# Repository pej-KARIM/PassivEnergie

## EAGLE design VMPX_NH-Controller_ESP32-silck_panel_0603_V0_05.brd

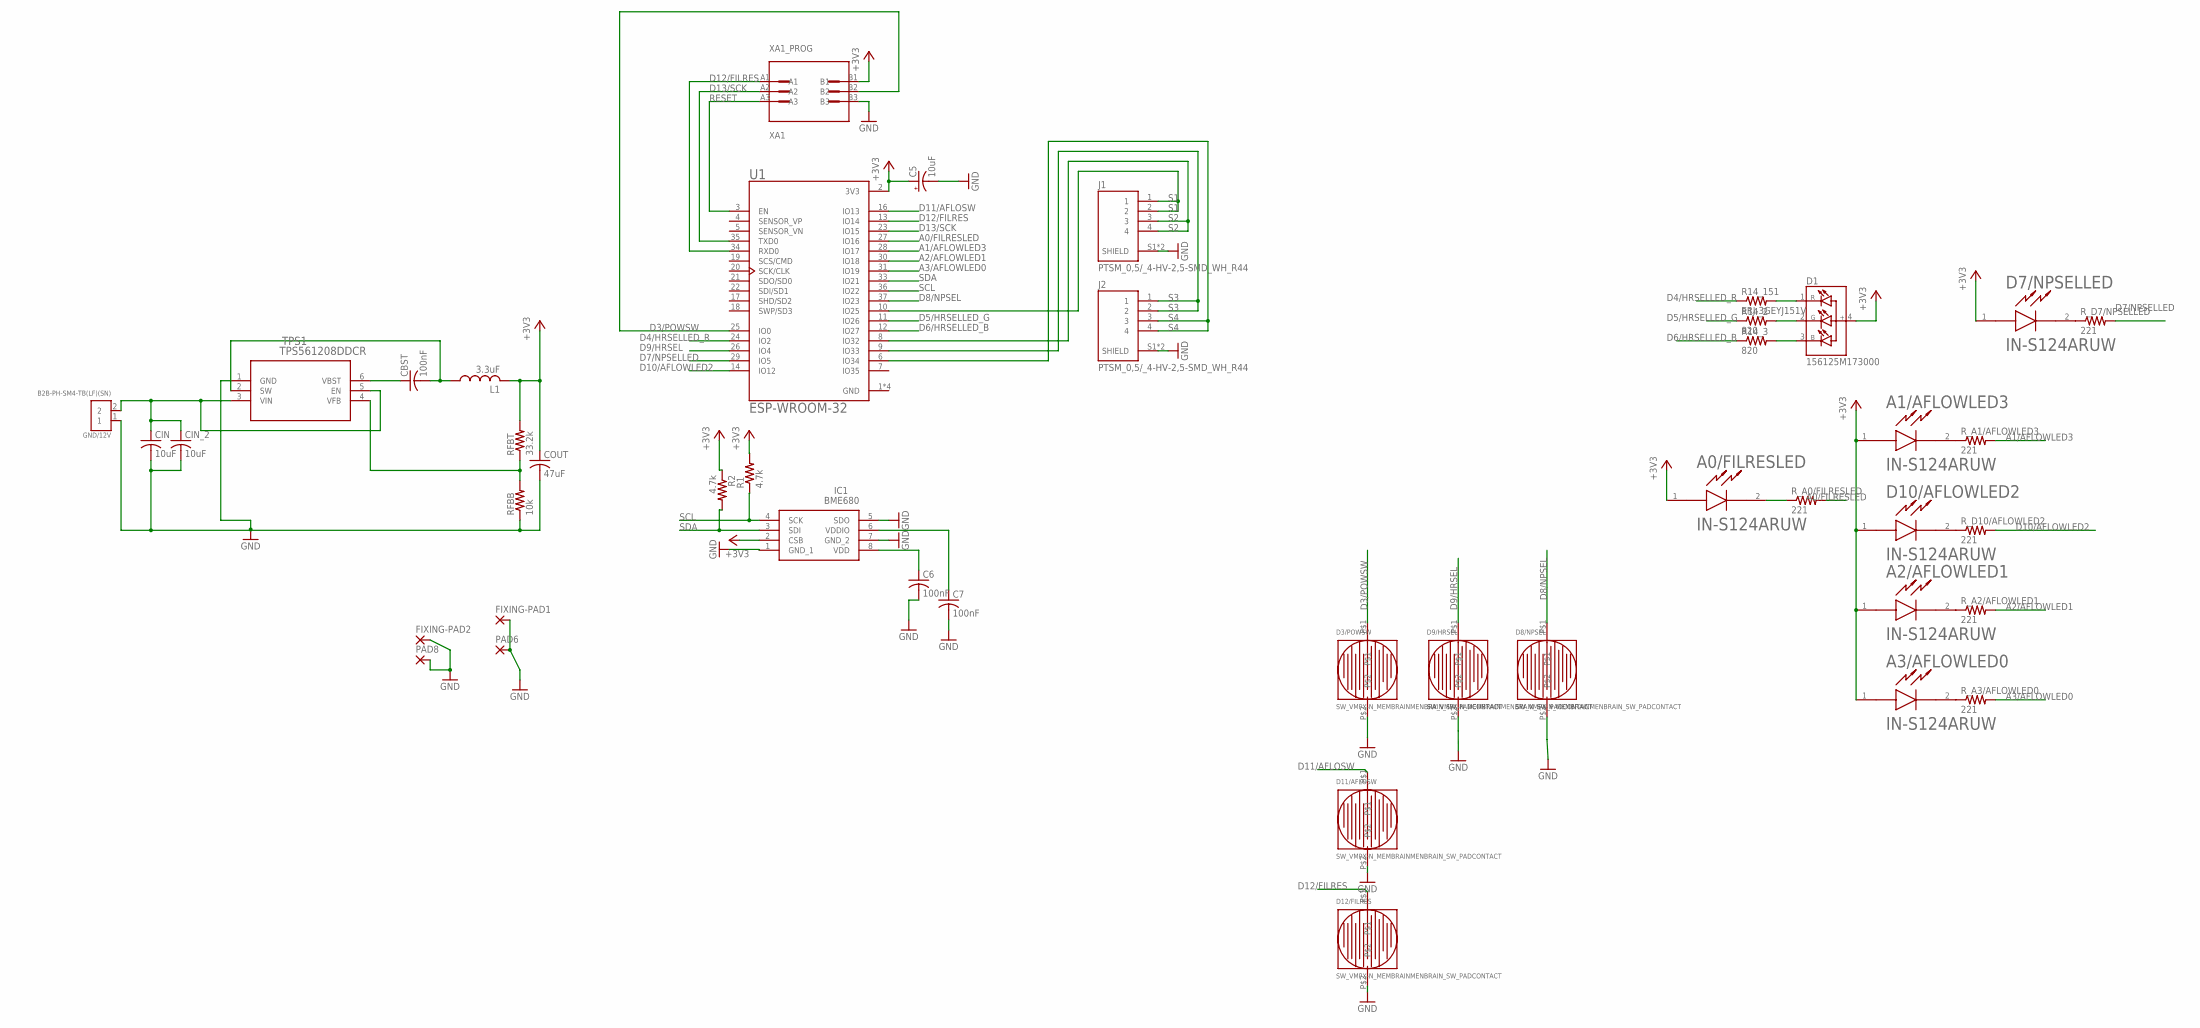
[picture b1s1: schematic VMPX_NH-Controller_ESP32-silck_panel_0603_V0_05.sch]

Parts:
A0/FILRESLED, A1/AFLOWLED3, A2/AFLOWLED1, A3/AFLOWLED0: IN-S124ARUW; LED_IN-S124ARUW
C5: 10uF; EIA3216
C6, C7: 100nF; C0603
CBST: 100nF; C0603
CIN: 10uF; C0603
CIN_2: 10uF; C0603
COUT: 47uF; C0603
D1: 156125M173000; LED_156125M173000
D3/POWSW, D8/NPSEL, D9/HRSEL, D11/AFLOSW, D12/FILRES: SW_VMPX-N_MEMBRAINMENBRAIN_SW_PADCONTACT; MENBRANSWITCHCONTACT
D7/NPSELLED, D10/AFLOWLED2: IN-S124ARUW; LED_IN-S124ARUW
FIXING-PAD1, FIXING-PAD2: SMD5; SMD2,54-5,08
GND/12V: B2B-PH-SM4-TB(LF)(SN); JST_B2B-PH-SM4-TB(LF)(SN)
IC1: BME680
J1, J2: PTSM_0,5/_4-HV-2,5-SMD_WH_R44; PHOENIX_PTSM_0,5/_4-HV-2,5-SMD_WH_R44
L1: 3.3uF; L2012C
PAD6, PAD8: SMD5; SMD2,54-5,08
R1, R2: 4.7k; RESC1608X55
R14_2, R14_3: 820; RESC1608X55
R14_151: ERJ-3GEYJ151V; RESC1608X55
RFBB: 10k; R0603
RFBT: 33.2k; R0603
R_A0/FILRESLED, R_A1/AFLOWLED3, R_A2/AFLOWLED1, R_A3/AFLOWLED0: 221; RESC1608X55
R_D7/NPSELLED, R_D10/AFLOWLED2: 221; RESC1608X55
TPS1: TPS561208DDCR; DDC6
U1: ESP-WROOM-32; MODULE_ESP-WROOM-32
XA1_PROG: XA1; TE_5-146130-2

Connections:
+3V3: A0/FILRESLED.1 (A), A1/AFLOWLED3.1 (A), A2/AFLOWLED1.1 (A), A3/AFLOWLED0.1 (A), C5.A (+), COUT.1, D1.4 (+), D7/NPSELLED.1 (A), D10/AFLOWLED2.1 (A), IC1.2 (CSB), L1.2, R1.2, R2.1, RFBT.2, U1.2 (3V3), XA1_PROG.B1
A0/FILRESLED: R_A0/FILRESLED.2, U1.27 (IO16)
A1/AFLOWLED3: R_A1/AFLOWLED3.2, U1.28 (IO17)
A2/AFLOWLED1: R_A2/AFLOWLED1.2, U1.30 (IO18)
A3/AFLOWLED0: R_A3/AFLOWLED0.2, U1.31 (IO19)
D3/POWSW: D3/POWSW.P$1, U1.25 (IO0), XA1_PROG.B2
D4/HRSELLED_R: R14_151.1, U1.24 (IO2)
D5/HRSELLED_G: R14_2.1, U1.11 (IO26)
D6/HRSELLED_B: R14_3.1, U1.12 (IO27)
D7/NPSELLED: R_D7/NPSELLED.2, U1.29 (IO5)
D8/NPSEL: D8/NPSEL.P$1, U1.37 (IO23)
D9/HRSEL: D9/HRSEL.P$1, U1.26 (IO4)
D10/AFLOWLED2: R_D10/AFLOWLED2.2, U1.14 (IO12)
D11/AFLOSW: D11/AFLOSW.P$1, U1.16 (IO13)
D12/FILRES: D12/FILRES.P$1, U1.13 (IO14), U1.34 (RXD0), XA1_PROG.A1
D13/SCK: U1.23 (IO15), U1.35 (TXD0), XA1_PROG.A2
GND: C5.C (-), C6.2, C7.2, CIN.2, CIN_2.2, COUT.2, D3/POWSW.P$2, D8/NPSEL.P$2, D9/HRSEL.P$2, D11/AFLOSW.P$2, D12/FILRES.P$2, FIXING-PAD1.1, FIXING-PAD2.1, GND/12V.1, IC1.1 (GND_1), IC1.5 (SDO), IC1.7 (GND_2), J1.S1 (SHIELD), J1.S2 (SHIELD), J2.S1 (SHIELD), J2.S2 (SHIELD), PAD6.1, PAD8.1, RFBB.1, TPS1.1 (GND), U1.1 (GND), U1.1.1 (GND), U1.15 (GND), U1.38 (GND), XA1_PROG.B3
unnamed: A0/FILRESLED.2 (C), R_A0/FILRESLED.1
unnamed: C6.1, IC1.8 (VDD)
unnamed: D1.2 (G-), R14_2.2
unnamed: C7.1, IC1.6 (VDDIO)
unnamed: D1.3 (B-), R14_3.2
unnamed: D1.1 (R-), R14_151.2
unnamed: D7/NPSELLED.2 (C), R_D7/NPSELLED.1
unnamed: D10/AFLOWLED2.2 (C), R_D10/AFLOWLED2.1
unnamed: A1/AFLOWLED3.2 (C), R_A1/AFLOWLED3.1
unnamed: A2/AFLOWLED1.2 (C), R_A2/AFLOWLED1.1
unnamed: A3/AFLOWLED0.2 (C), R_A3/AFLOWLED0.1
RESET: U1.3 (EN), XA1_PROG.A3
S1: J1.1, J1.2, U1.10 (IO25)
S2: J1.3, J1.4, U1.8 (IO32)
S3: J2.1, J2.2, U1.9 (IO33)
S4: J2.3, J2.4, U1.6 (IO34)
SCL: IC1.4 (SCK), R1.1, U1.36 (IO22)
SDA: IC1.3 (SDI), R2.2, U1.33 (IO21)
SW: CBST.2, L1.1, TPS1.2 (SW)
VBF: RFBB.2, RFBT.1, TPS1.4 (VFB)
VBST: CBST.1, TPS1.6 (VBST)
VIN: CIN.1, CIN_2.1, GND/12V.2, TPS1.3 (VIN), TPS1.5 (EN)

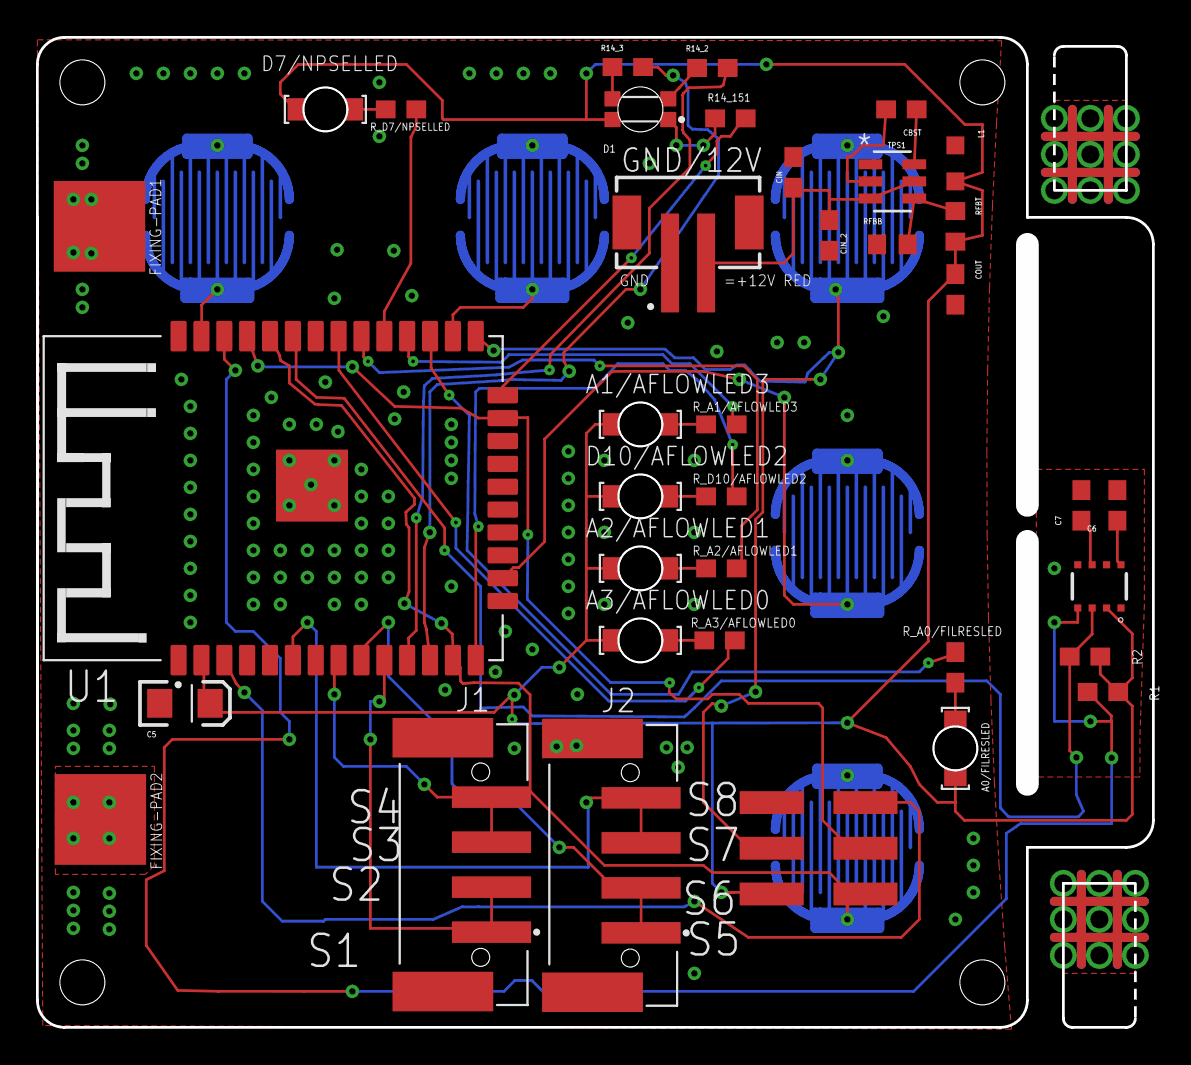
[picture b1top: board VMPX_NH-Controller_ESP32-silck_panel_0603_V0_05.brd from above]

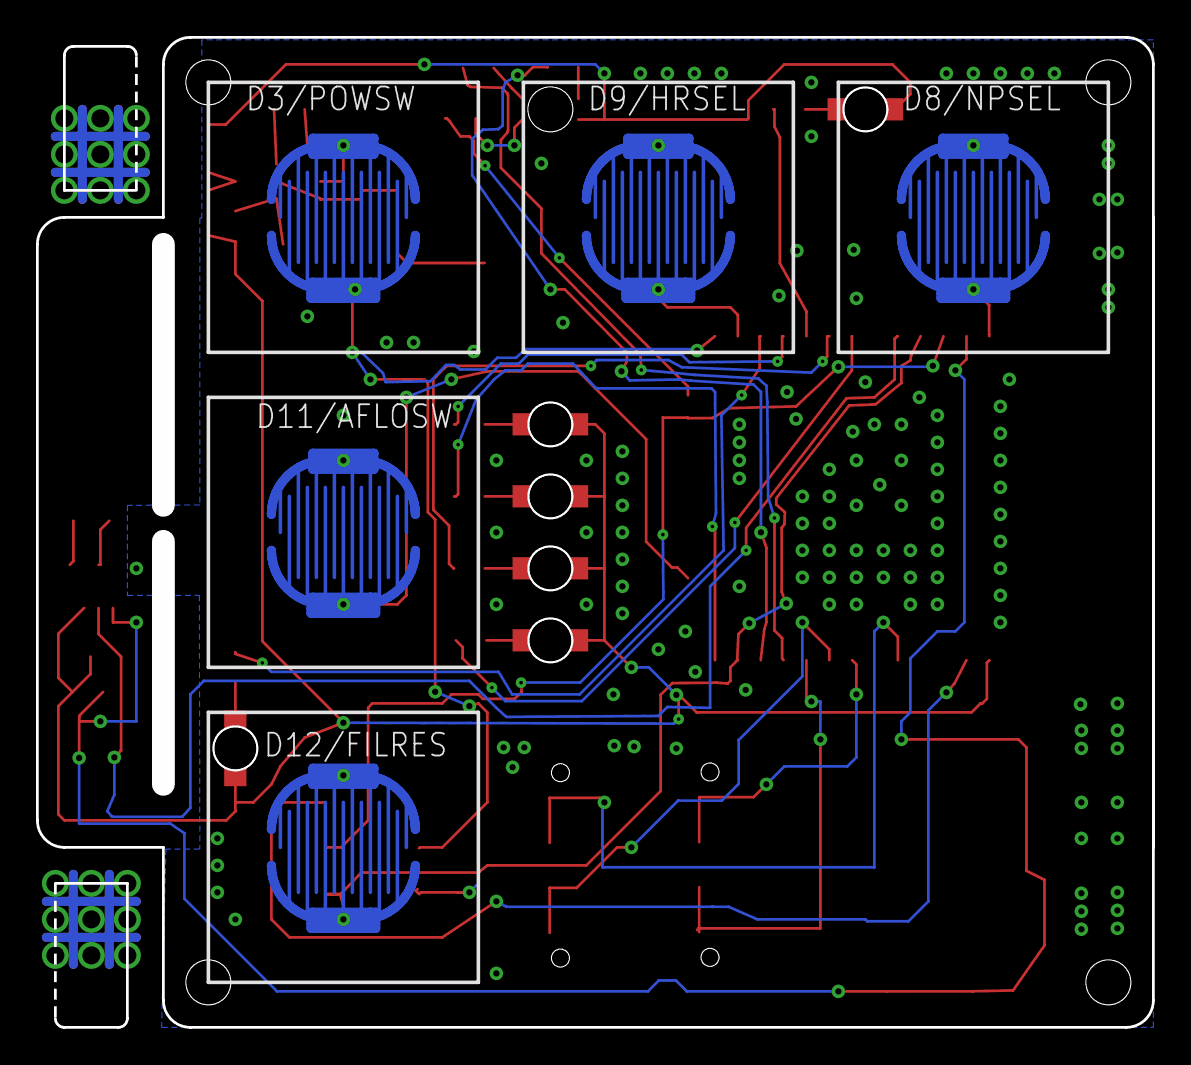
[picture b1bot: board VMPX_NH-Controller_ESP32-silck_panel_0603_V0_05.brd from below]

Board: 2 copper layers, 60.9 x 53.9 mm, 44 parts (5 on the bottom side), 39 nets.

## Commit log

2019-05-24 Add files via upload
    VMPX-NH-IoT PCB Design Update

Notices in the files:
parts and their libraries:
SparkFun-Retired: Licensing: Creative Commons ShareAlike 4.0 International - https://creativecommons.org/licenses/by-sa/4.0
